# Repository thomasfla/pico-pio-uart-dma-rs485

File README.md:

# pico-pio-uart-dma-rs485

Implementing multiple channel RS485 using Raspberry Pi Pico PIO and DMA.
This was inteded for low latency comunication with robotics actuator and sensors.

- For half-duplex RS485: only one device transmits at a time.
- The OE (Output Enable) pin controls RS485 driver direction.
- Supports multiple channels via separate PIO state machines.
- Tested at high baud rates (12.5 Mbps and likely higher).
- Waits for response with a configurable timeout.
- End-of-frame detection based on silence (similar to Modbus).
- Fully offloaded TX and RX: the CPU is not involved during transmission and reception of complete frames and responses.

## Arduino Library

An Arduino-friendly packaging of this driver lives in `arduino/PicoPioRs485/`. Copy that folder into your Arduino `libraries` directory (or use **Sketch → Include Library → Add .ZIP Library…** from the IDE). The library exposes the `RS485_Config`/`rs485_*` helpers as well as a small `PicoPioRs485` C++ class so sketches can `begin()`, queue a packet, send it, and wait for the optional response.

Bundled examples:

- `LoopbackMinimal`: drives two PIO state machines on the same Pico so you can quickly wire a master/responder pair and watch the returned bytes over USB serial.
- `BaudRateSwitch`: shows how to retune the RS485 link speed interactively from the serial monitor.

Both sketches are intentionally smaller and simpler than the original `examples/basic/main*.c` demos so you can focus on the Arduino APIs.

## Building

Make sure you have the [Pico SDK](https://github.com/raspberrypi/pico-sdk) installed and initialized.

```sh
mkdir build
cd build
cmake ..
make
```

## Flashing

### Option 1: Drag-and-drop UF2

1. Hold the BOOTSEL button on your Pico and connect it to your computer via USB.
2. Release the button. The Pico will appear as a USB drive.
3. Copy the generated `.uf2` file from `build/examples/basic/` to the Pico drive.

### Option 2: Using `picotool`

## How It Works

Each RS485 channel uses a single PIO state machine to handle both reception and transmission in half-duplex. When we want to send a frame, we provide the data, the length of the frame, and the timeout to wait for a response. Everything else is handled automatically by the PIO and DMA.

First, the state machine takes care of transmitting the frame. It enables the driver (OE pin) during the send, then disables it when done. Right after that, it starts listening for a response. If a response comes in, the bytes are written directly into memory using DMA, without the CPU being involved. If there's no response, it waits until the timeout expires.

At any point, we can poll the state of the state machine to check if the transmission and reception are complete. We can also look at the DMA pointer to see how many bytes have been received. This way, the CPU only gets involved before and after the frame exchange.

### Limitations:

- At high baud rates, it is important that the PIO clock divisor is an integer or close to one. We can adjust the system clock to achieve that.

- The PIO runs at 8 times the baud rate. For example, with a 200 MHz system clock, the baud rate is limited to around 25 MHz.

- RX sampling uses non-blocking edge detection in the PIO to allow both timeout tracking and pin monitoring of a Start bit. This introduces a one-instruction jitter in the sampling time.

- Currently, no interrupt is generated after transmission, but it should be easy to add one.

- If the received frame is not a multiple of 32 bits, it will be padded with zeros before being sent to the DMA. We have no way to know the exact frame size, since it will be rounded up to the next multiple of 32 bits.

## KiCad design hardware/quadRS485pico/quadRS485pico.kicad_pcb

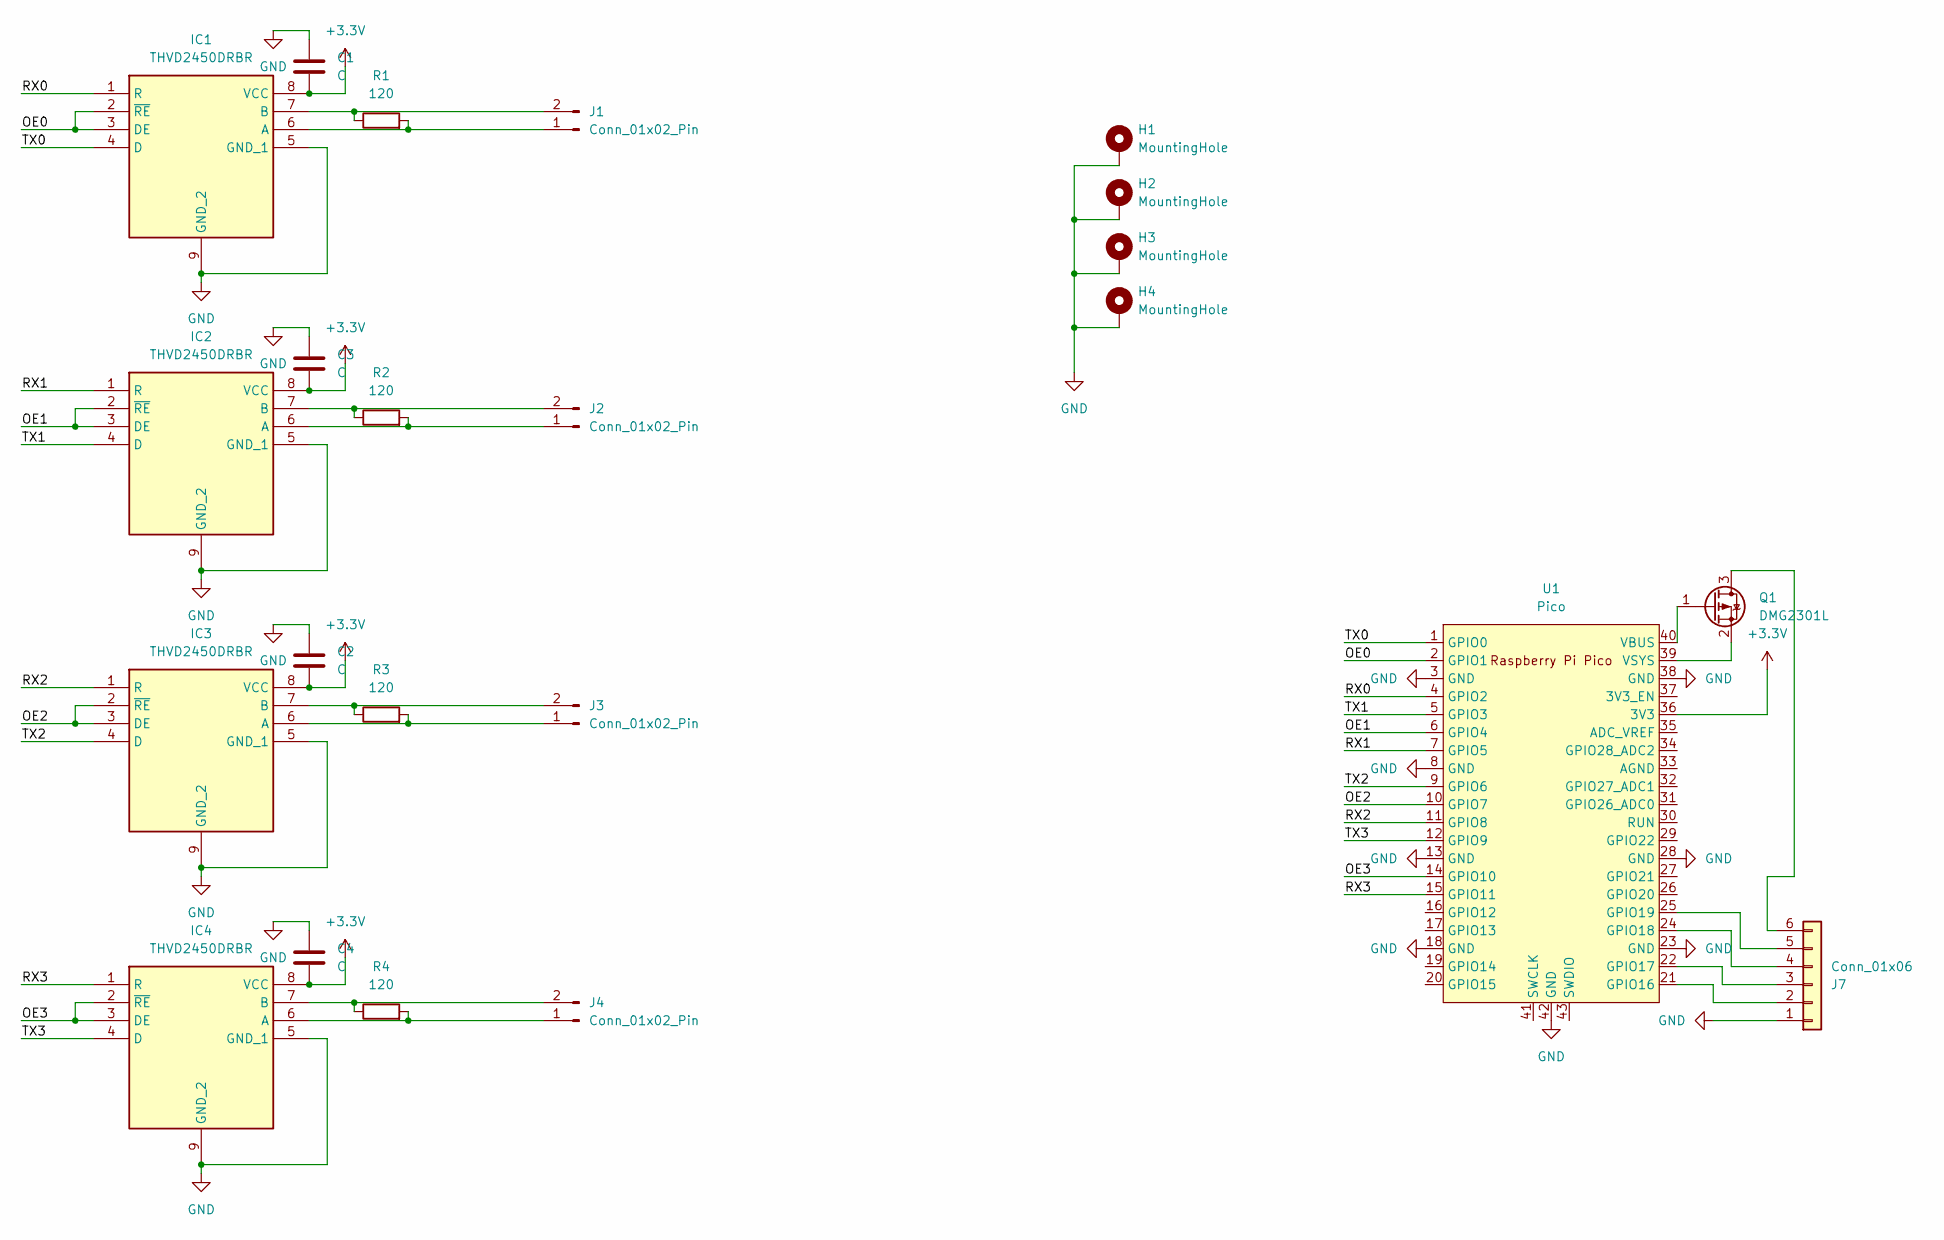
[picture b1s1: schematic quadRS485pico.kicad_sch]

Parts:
C1, C2, C3, C4: C; C_0603_1608Metric
H1, H2, H3, H4: MountingHole; MountingHole_2.5mm_Pad_TopBottom
IC1, IC2, IC3, IC4: THVD2450DRBR; SON65P300X300X100-9N; Manufacturer_Part_Number THVD2450DRBR; Mouser Part Number 595-THVD2450DRBR
J1, J2, J3, J4: Conn_01x02_Pin; Hirose_DF13-02P-1.25DSA_1x02_P1.25mm_Vertical
J7: Conn_01x06; Hirose_DF13-06P-1.25DSA_1x06_P1.25mm_Vertical
Q1: DMG2301L; SOT-23
R1, R2, R3, R4: 120; R_0603_1608Metric
U1: Pico; RPi_Pico_SMD_TH

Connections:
+3.3V: C1.2, C2.2, C3.2, C4.2, IC1.8 (VCC), IC2.8 (VCC), IC3.8 (VCC), IC4.8 (VCC), U1.36 (3V3)
/OE0: IC1.2 (~RE), IC1.3 (DE), U1.2 (GPIO1)
/OE1: IC2.2 (~RE), IC2.3 (DE), U1.6 (GPIO4)
/OE2: IC3.2 (~RE), IC3.3 (DE), U1.10 (GPIO7)
/OE3: IC4.2 (~RE), IC4.3 (DE), U1.14 (GPIO10)
/RX0: IC1.1 (R), U1.4 (GPIO2)
/RX1: IC2.1 (R), U1.7 (GPIO5)
/RX2: IC3.1 (R), U1.11 (GPIO8)
/RX3: IC4.1 (R), U1.15 (GPIO11)
/TX0: IC1.4 (D), U1.1 (GPIO0)
/TX1: IC2.4 (D), U1.5 (GPIO3)
/TX2: IC3.4 (D), U1.9 (GPIO6)
/TX3: IC4.4 (D), U1.12 (GPIO9)
GND: C1.1, C2.1, C3.1, C4.1, H1.1, H2.1, H3.1, H4.1, IC1.5 (GND_1), IC1.9 (GND_2), IC2.5 (GND_1), IC2.9 (GND_2), IC3.5 (GND_1), IC3.9 (GND_2), IC4.5 (GND_1), IC4.9 (GND_2), J7.1, U1.3 (GND), U1.8 (GND), U1.13 (GND), U1.18 (GND), U1.23 (GND), U1.28 (GND), U1.38 (GND), U1.42 (GND)
unnamed: IC1.6 (A), J1.1, R1.2
unnamed: IC1.7 (B), J1.2, R1.1
unnamed: IC2.6 (A), J2.1, R2.2
unnamed: IC2.7 (B), J2.2, R2.1
unnamed: IC3.6 (A), J3.1, R3.2
unnamed: IC3.7 (B), J3.2, R3.1
unnamed: IC4.6 (A), J4.1, R4.2
unnamed: IC4.7 (B), J4.2, R4.1
unnamed: J7.2, U1.21 (GPIO16)
unnamed: J7.3, U1.22 (GPIO17)
unnamed: J7.4, U1.24 (GPIO18)
unnamed: J7.5, U1.25 (GPIO19)
unnamed: J7.6, Q1.3 (D)
unnamed: Q1.1 (G), U1.40 (VBUS)
unnamed: Q1.2 (S), U1.39 (VSYS)

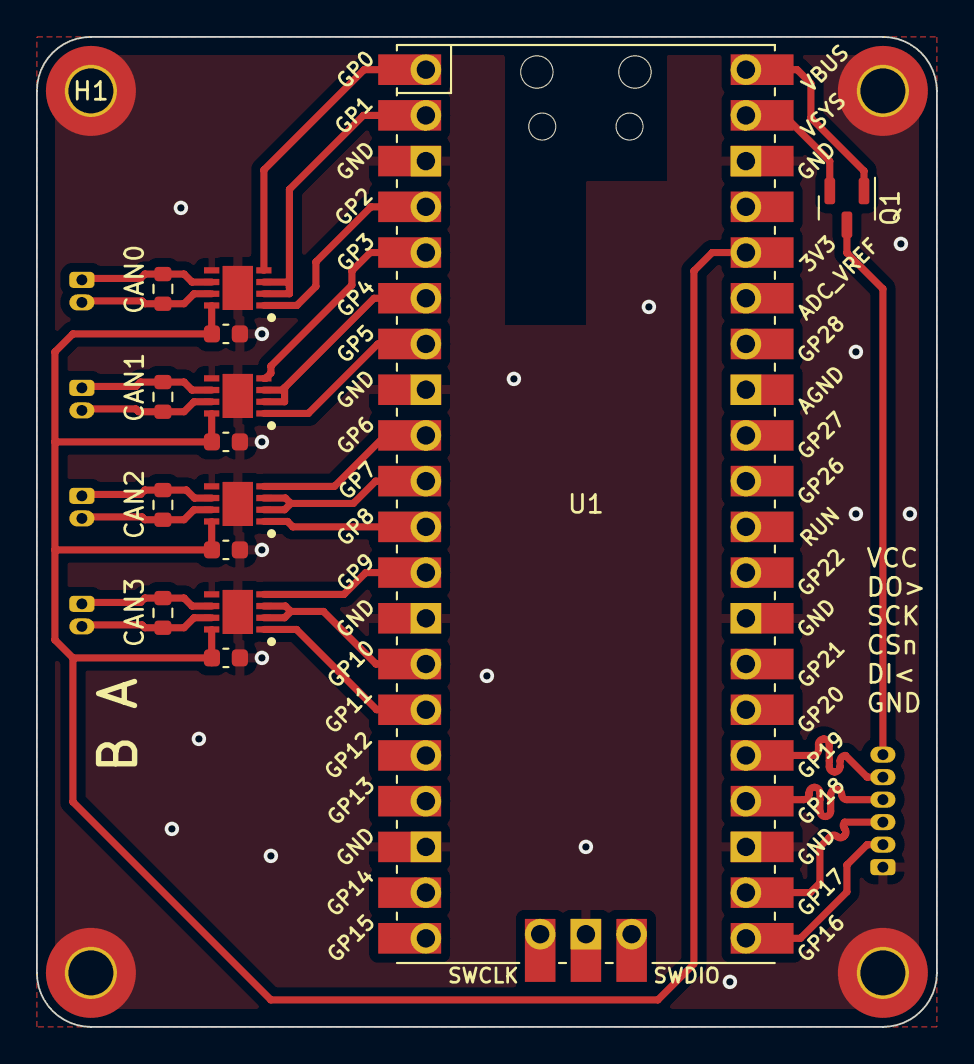
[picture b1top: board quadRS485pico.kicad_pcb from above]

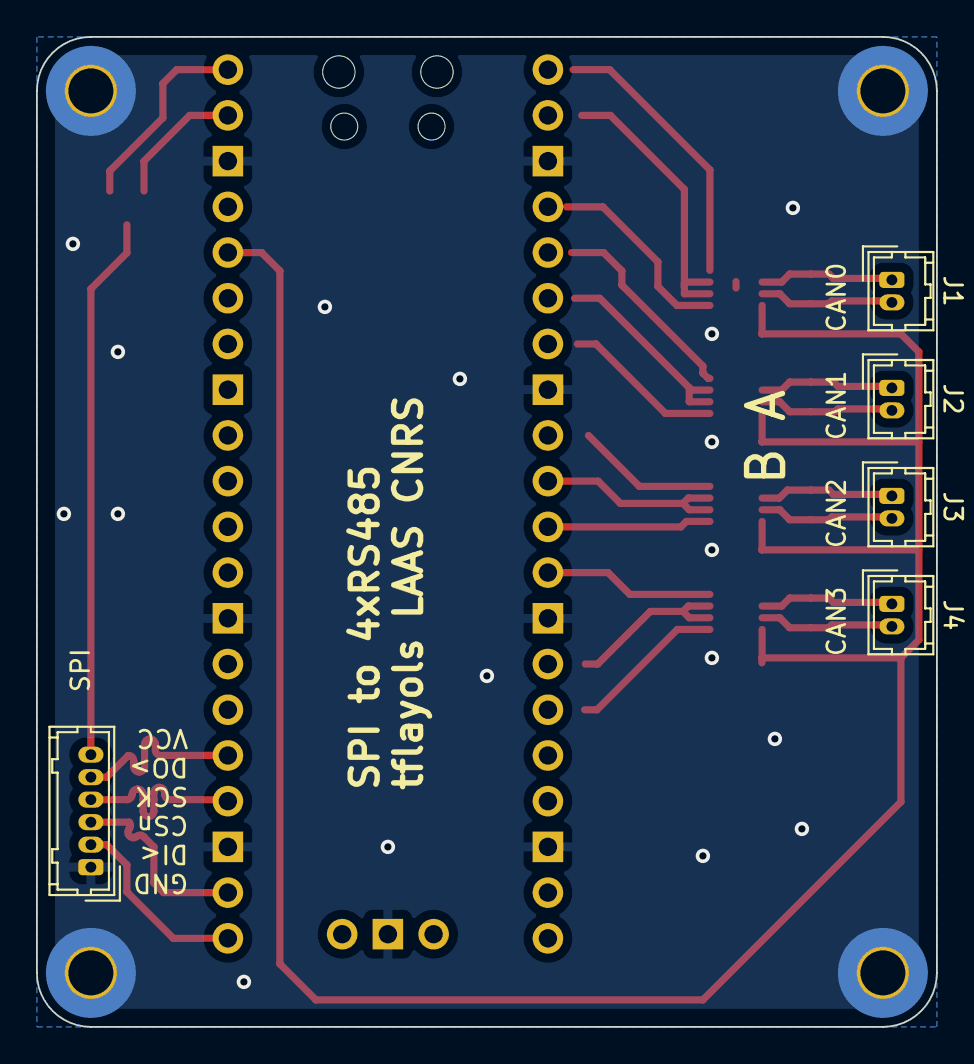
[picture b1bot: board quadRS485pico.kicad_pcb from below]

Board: 2 copper layers, 50.0 x 55.0 mm, 23 parts (5 on the bottom side), 29 nets.

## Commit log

2023-09-06 first attempt dosent work
2023-09-18 Working version with DMA, just missing end of transmission interupt
2023-09-18 use a loop for the 8 bits
2023-09-21 Implement RX, this works, but still missing the RX DMA
2023-09-21 Pull as early as possible, without this, at very high baud rate (like 10Mbps), we can be waiting for the DMA and have a longer start bit.
2023-09-22 add DMA for RX, switch to using 32bits transfers to optimize memory transfer; seems to work fine
2023-09-26 cleanup, optimise PIO program for size, tested at 12Mbaud with no issues.
2023-10-05 add hardware design for testing 4 rs485 lines
2023-11-15 set pinout according to the hardware design in the code, add a endless loop after RX in PIO program
2023-11-21 Move RS485 code to a library, define a configure structure for it
2023-11-22 Create a function to construct the data for PIO
2023-11-22 add missing library files
2024-01-10 Adapt main to do test with omodri motor driver adress 42, sinus position command
2024-08-09 add pinout info, add vias, make it double side, clean the board
2024-08-27 Fix pinout label for B A
2025-05-28 Fix a bug on length of data logic, Clean the library, add function to send, receive packets, clean the example, implement multichanel (up to 12)
2025-06-03 Split the example from the library
2025-06-03 cleanup, add doc, switch to latest picosdk
2025-06-03 Add missing CMakeLists.txt
2025-06-10 Make timeout a parameter of rs485_prepare_tx_packet
2025-12-19 make it arduino compatible
